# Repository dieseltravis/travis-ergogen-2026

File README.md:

# Travis's Ergogen v2026
This is a split keyboard with 2 ortholinear symmetrical 40-key halfs made with Ergogen v4. Multiple positions for an i2c OLED and mousewheel encoder. TRRS for connecting halfs, firmware not updated for that yet though.

## Parts:

JLCPCB SMD components (40 each per board):
* capacitor C710467
* diode C7420318
* RGB LED C5378731
* MX C41430893

Other parts:
* MCU: RP2040 Community Edition
* capacitor 6.3V 1000uF
* resistors 510k ohm (2 per board)
* 2u stabilizers (2 per board)
* TRRS PJ-320A jacks (2 per board if connecting)
* mousewheel encoder (like Alps-EC10E1220501)
* OLED i2c
* MX switches (40 per board)
* low-profile sockets/pins for MCU & OLED

## References:
My previous ergogen abominations:
* [travis-ergogen-numpad](https://github.com/dieseltravis/travis-ergogen-numpad)
* [travis-ergogen-2024](https://github.com/dieseltravis/travis-ergogen-2024)

### Footprints:
* https://github.com/ceoloide/ergogen-footprints
* https://github.com/dieseltravis/ergogen-footprints-travis

## Tips:

### Font used:
```
brew install --cask font-3270-nerd-font
```
https://www.nerdfonts.com/font-downloads

### Routing widths used:
```
"track_widths": [
        0.0,
        0.254,
        0.3556,
        0.508,
        1.27
      ],
```

### For STL arcs
It is buggy, set toJscadScript's maxArcFacet in Ergogen's cases.js, example locations on my machine:
```
./node_modules/ergogen/src/cases.js
~/.local/share/mise/installs/node/24.13.0/lib/node_modules/ergogen/src/cases.js
```
Note: the arcs are *super* glitchy in STLs

### For weird `node\r:` error:
```
find ./node_modules/ -type f -print0 | xargs -0 dos2unix --
```

## TODO:
* ~board: make those weird bottom shapes nicer~
* plate: print a 2u stab test key
    * ~print a top key test to measure for interference with i2c~
* ~i2c: if plate doesn't interfere with bottom ones remove top ones~
    * ~trrs: if top ones are removed, move left trrs to left side~
* case: just use flat one, arcs get too glitchy
* ~routing~
* ~bom: use [kicad-jlcpcb-tools plugin](https://github.com/Bouni/kicad-jlcpcb-tools)~
* ~leds: generate positions~
* ~qmk firmware~
    * ~via support~
* then arrowpad

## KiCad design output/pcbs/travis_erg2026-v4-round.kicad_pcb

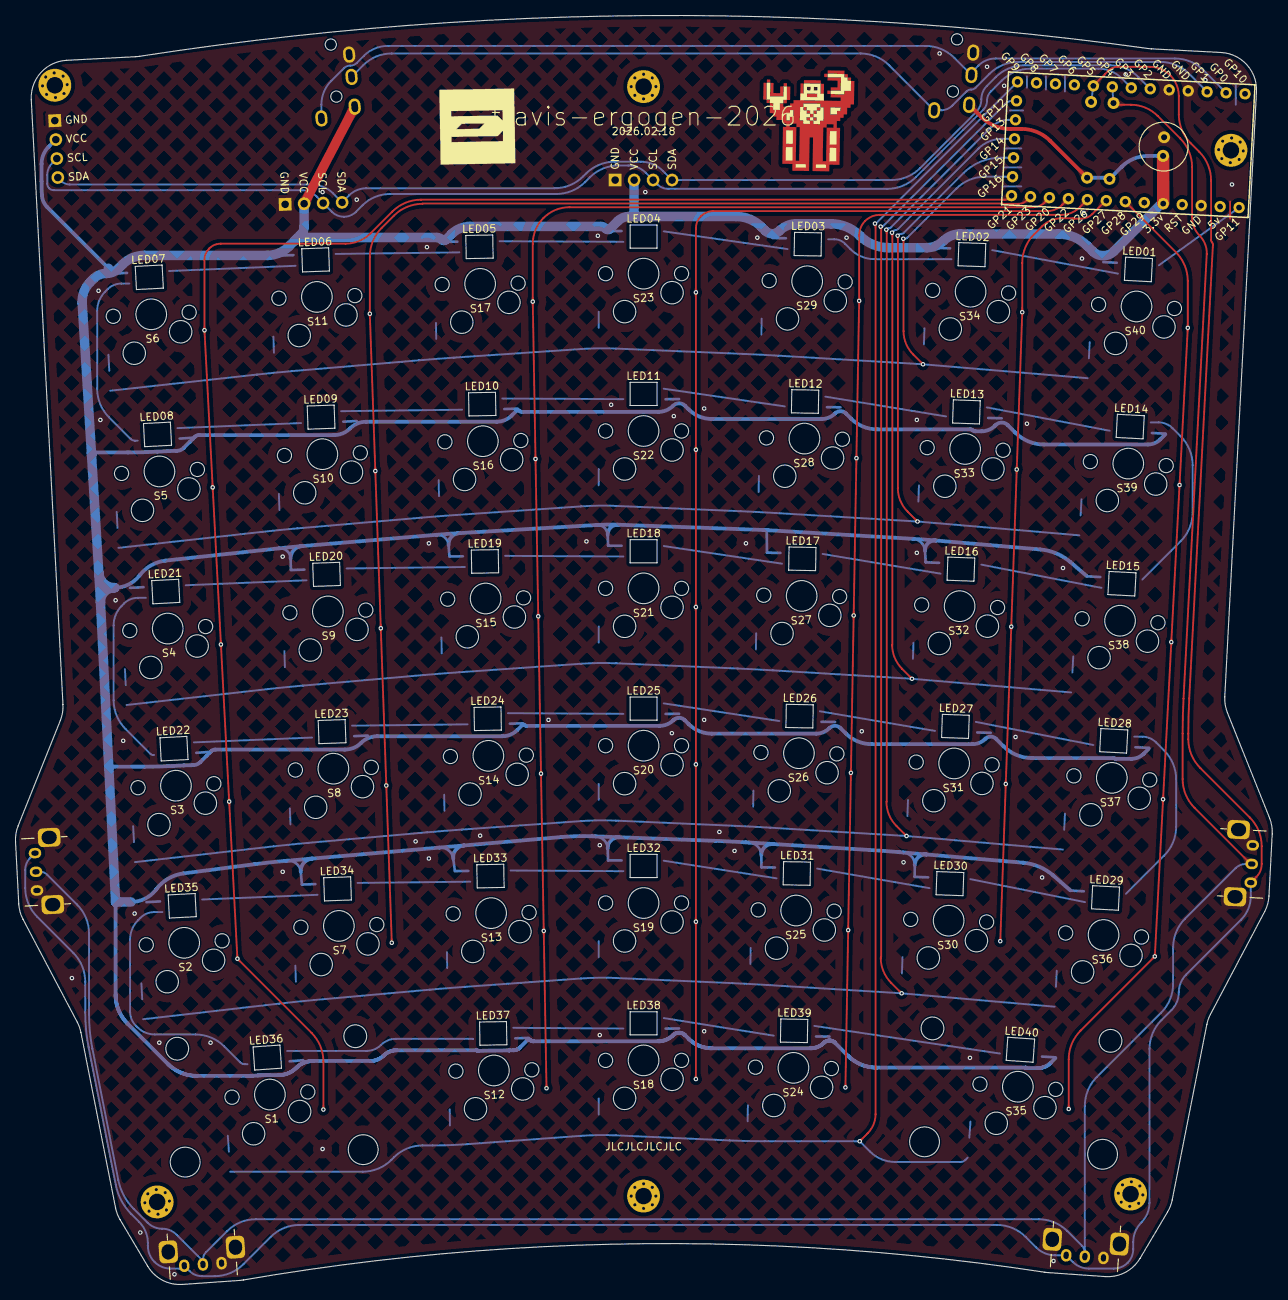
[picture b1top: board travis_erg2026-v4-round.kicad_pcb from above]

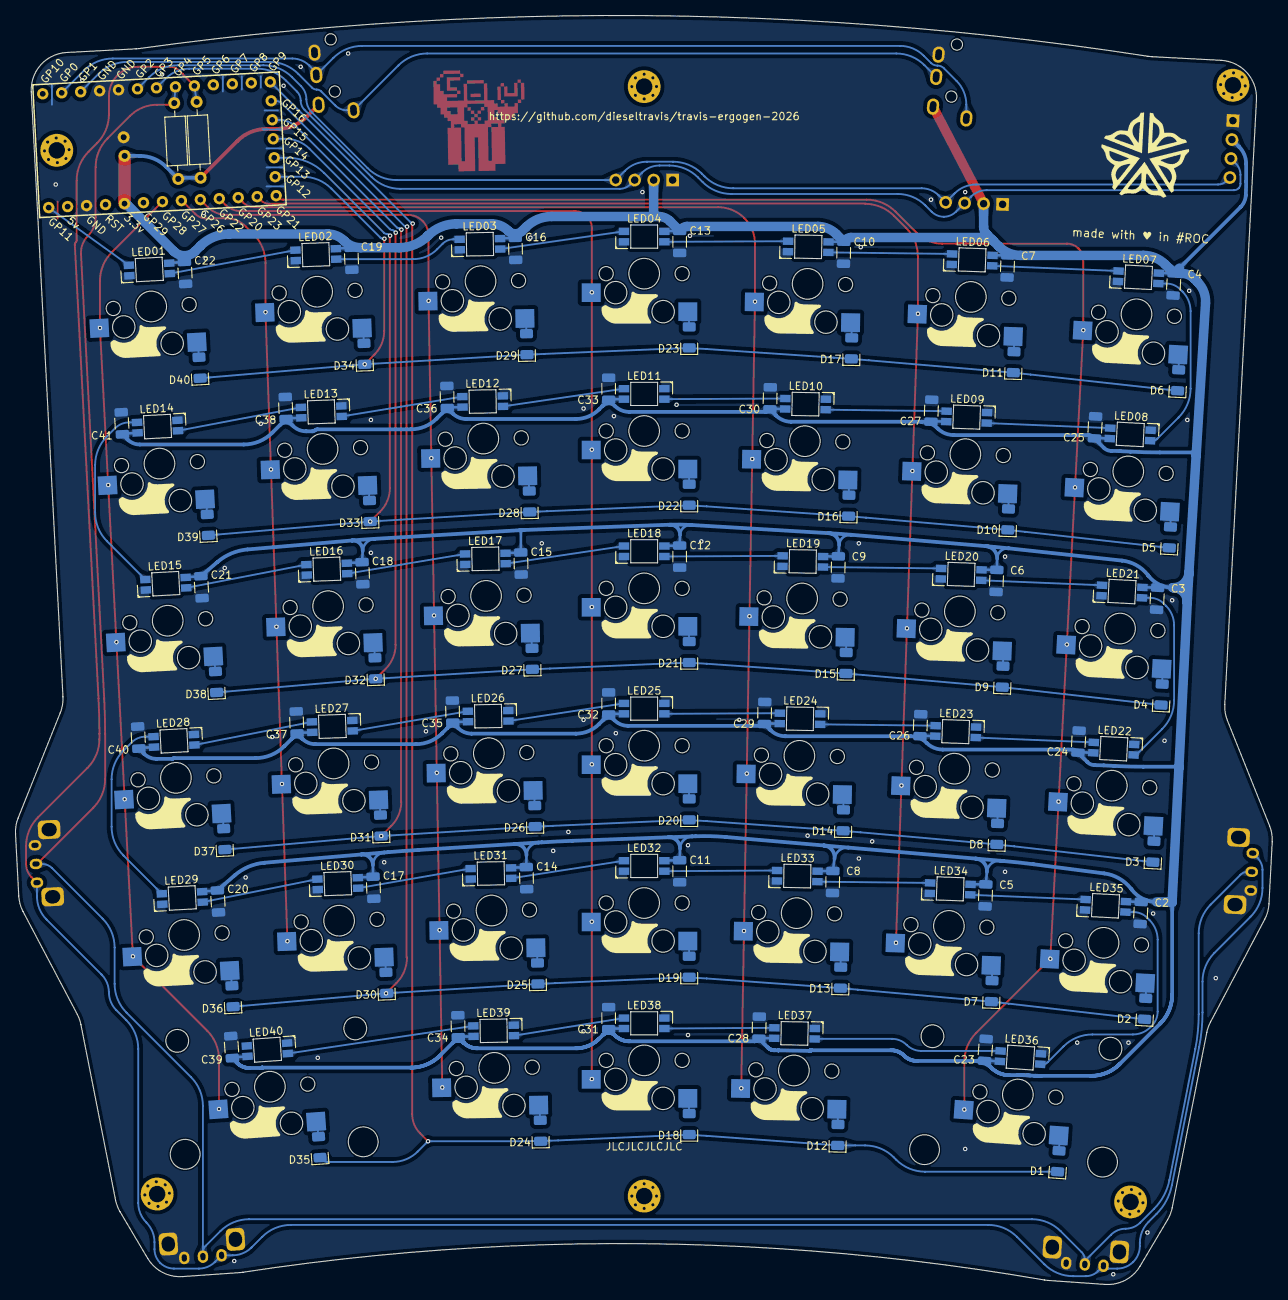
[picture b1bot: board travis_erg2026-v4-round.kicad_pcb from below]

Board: 2 copper layers, 168.1 x 169.8 mm, 184 parts (163 on the bottom side), 101 nets.

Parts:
C1: 6.3V 1000uF; C_Radial_D6.3mm_H11.0mm_P2.50mm
C2, C3, C4, C5, C6, C7, C8, C9, C10, C11, C12, C13, C14, C15, C16, C17, C18, C19, C20, C21, C22, C23, C24, C25, C26, C27, C28, C29, C30, C31, C32, C33, C34, C35, C36, C37, C38, C39, C40, C41: C710467; C_1206_3216Metric
D1, D2, D3, D4, D5, D6, D7, D8, D9, D10, D11, D12, D13, D14, D15, D16, D17, D18, D19, D20, D21, D22, D23, D24, D25, D26, D27, D28, D29, D30, D31, D32, D33, D34, D35, D36, D37, D38, D39, D40: C7420318; D_1206_3216Metric
HOLE1, HOLE2, HOLE3, HOLE4, HOLE5, HOLE6: MountingHole_2.2mm_M2_Pad_Via
LED01, LED02, LED03, LED04, LED05, LED06, LED07, LED08, LED09, LED10, LED11, LED12, LED13, LED14, LED15, LED16, LED17, LED18, LED19, LED20, LED21, LED22, LED23, LED24, LED25, LED26, LED27, LED28, LED29, LED30, LED31, LED32, LED33, LED34, LED35, LED36, LED37, LED38, LED39, LED40: C5378731; led_SK6812mini-e (per-key, single-side)
LOGO1: utility_ergogen_logo
LOGO2: travis
MCU1: RP2040 Community Edition; RP2040_Pro_Micro
OLED1, OLED2, OLED3: I2C_Breakout
R1, R2: 510k; R_Axial_DIN0207_L6.3mm_D2.5mm_P10.16mm_Horizontal
ROC1: travis
ROT1, ROT2, ROT3, ROT4: EC10E1220501; Alps-EC10E1220501
S1, S2, S3, S4, S5, S6, S7, S8, S9, S10, S11, S12, S13, S14, S15, S16, S17, S18, S19, S20, S21, S22, S23, S24, S25, S26, S27, S28, S29, S30, S31, S32, S33, S34, S35, S36, S37, S38, S39, S40: C41430893; switch_mx
STAB2u1, STAB2u2: Stabilizer_MX_2.00u
TRRS1, TRRS2: trrs_pj320a

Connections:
GND: C1.2, C2.2, C3.2, C4.2, C5.2, C6.2, C7.2, C8.2, C9.2, C10.2, C11.2, C12.2, C13.2, C14.2, C15.2, C16.2, C17.2, C18.2, C19.2, C20.2, C21.2, C22.2, C23.2, C24.2, C25.2, C26.2, C27.2, C28.2, C29.2, C30.2, C31.2, C32.2, C33.2, C34.2, C35.2, C36.2, C37.2, C38.2, C39.2, C40.2, C41.2, LED01.3, LED02.3, LED03.3, LED04.3, LED05.3, LED06.3, LED07.3, LED08.3, LED09.3, LED10.3, LED11.3, LED12.3, LED13.3, LED14.3, LED15.3, LED16.3, LED17.3, LED18.3, LED19.3, LED20.3, LED21.3, LED22.3, LED23.3, LED24.3, LED25.3, LED26.3, LED27.3, LED28.3, LED29.3, LED30.3, LED31.3, LED32.3, LED33.3, LED34.3, LED35.3, LED36.3, LED37.3, LED38.3, LED39.3, LED40.3, MCU1.4, MCU1.5, MCU1.29, OLED1.1, OLED2.1, OLED3.1, ROT1.4, ROT1.C, ROT2.4, ROT2.C, ROT3.4, ROT3.C, ROT4.4, ROT4.C, TRRS1.2, TRRS2.2
LED01: LED01.4, MCU1.31
LED02: LED01.2, LED02.4
LED03: LED02.2, LED03.4
LED04: LED03.2, LED04.4
LED05: LED04.2, LED05.4
LED06: LED05.2, LED06.4
LED07: LED06.2, LED07.4
LED08: LED07.2, LED08.4
LED09: LED08.2, LED09.4
LED10: LED09.2, LED10.4
LED11: LED10.2, LED11.4
LED12: LED11.2, LED12.4
LED13: LED12.2, LED13.4
LED14: LED13.2, LED14.4
LED15: LED14.2, LED15.4
LED16: LED15.2, LED16.4
LED17: LED16.2, LED17.4
LED18: LED17.2, LED18.4
LED19: LED18.2, LED19.4
LED20: LED19.2, LED20.4
LED21: LED20.2, LED21.4
LED22: LED21.2, LED22.4
LED23: LED22.2, LED23.4
LED24: LED23.2, LED24.4
LED25: LED24.2, LED25.4
LED26: LED25.2, LED26.4
LED27: LED26.2, LED27.4
LED28: LED27.2, LED28.4
LED29: LED28.2, LED29.4
LED30: LED29.2, LED30.4
LED31: LED30.2, LED31.4
LED32: LED31.2, LED32.4
LED33: LED32.2, LED33.4
LED34: LED33.2, LED34.4
LED35: LED34.2, LED35.4
LED36: LED35.2, LED36.4
LED37: LED36.2, LED37.4
LED38: LED37.2, LED38.4
LED39: LED38.2, LED39.4
LED40: LED39.2, LED40.4
RX: MCU1.3, TRRS1.3, TRRS2.5
TX: MCU1.2, TRRS1.5, TRRS2.3
VCC: C1.1, C2.1, C3.1, C4.1, C5.1, C6.1, C7.1, C8.1, C9.1, C10.1, C11.1, C12.1, C13.1, C14.1, C15.1, C16.1, C17.1, C18.1, C19.1, C20.1, C21.1, C22.1, C23.1, C24.1, C25.1, C26.1, C27.1, C28.1, C29.1, C30.1, C31.1, C32.1, C33.1, C34.1, C35.1, C36.1, C37.1, C38.1, C39.1, C40.1, C41.1, LED01.1, LED02.1, LED03.1, LED04.1, LED05.1, LED06.1, LED07.1, LED08.1, LED09.1, LED10.1, LED11.1, LED12.1, LED13.1, LED14.1, LED15.1, LED16.1, LED17.1, LED18.1, LED19.1, LED20.1, LED21.1, LED22.1, LED23.1, LED24.1, LED25.1, LED26.1, LED27.1, LED28.1, LED29.1, LED30.1, LED31.1, LED32.1, LED33.1, LED34.1, LED35.1, LED36.1, LED37.1, LED38.1, LED39.1, LED40.1, MCU1.27, OLED1.2, OLED2.2, OLED3.2, R1.1, R2.1, TRRS1.4, TRRS2.4
col0: MCU1.19, S1.1, S2.1, S3.1, S4.1, S5.1, S6.1
col1: MCU1.20, S7.1, S8.1, S9.1, S10.1, S11.1
col2: MCU1.21, S12.1, S13.1, S14.1, S15.1, S16.1, S17.1
col3: MCU1.22, S18.1, S19.1, S20.1, S21.1, S22.1, S23.1
col4: MCU1.23, S24.1, S25.1, S26.1, S27.1, S28.1, S29.1
col5: MCU1.24, S30.1, S31.1, S32.1, S33.1, S34.1
col6: MCU1.25, S35.1, S36.1, S37.1, S38.1, S39.1, S40.1
encA: MCU1.9, R1.2, ROT1.A, ROT2.A, ROT3.A, ROT4.A
encB: MCU1.8, R2.2, ROT1.B, ROT2.B, ROT3.B, ROT4.B
matrix_col0_row0: D1.2, S1.2
matrix_col0_row1: D2.2, S2.2
matrix_col0_row2: D3.2, S3.2
matrix_col0_row3: D4.2, S4.2
matrix_col0_row4: D5.2, S5.2
matrix_col0_row5: D6.2, S6.2
matrix_col1_row1: D7.2, S7.2
matrix_col1_row2: D8.2, S8.2
matrix_col1_row3: D9.2, S9.2
matrix_col1_row4: D10.2, S10.2
matrix_col1_row5: D11.2, S11.2
matrix_col2_row0: D12.2, S12.2
matrix_col2_row1: D13.2, S13.2
matrix_col2_row2: D14.2, S14.2
matrix_col2_row3: D15.2, S15.2
matrix_col2_row4: D16.2, S16.2
matrix_col2_row5: D17.2, S17.2
matrix_col3_row0: D18.2, S18.2
matrix_col3_row1: D19.2, S19.2
matrix_col3_row2: D20.2, S20.2
matrix_col3_row3: D21.2, S21.2
matrix_col3_row4: D22.2, S22.2
matrix_col3_row5: D23.2, S23.2
matrix_col4_row0: D24.2, S24.2
matrix_col4_row1: D25.2, S25.2
matrix_col4_row2: D26.2, S26.2
matrix_col4_row3: D27.2, S27.2
matrix_col4_row4: D28.2, S28.2
matrix_col4_row5: D29.2, S29.2
matrix_col5_row1: D30.2, S30.2
matrix_col5_row2: D31.2, S31.2
matrix_col5_row3: D32.2, S32.2
matrix_col5_row4: D33.2, S33.2
matrix_col5_row5: D34.2, S34.2
matrix_col6_row0: D35.2, S35.2
matrix_col6_row1: D36.2, S36.2
matrix_col6_row2: D37.2, S37.2
matrix_col6_row3: D38.2, S38.2
matrix_col6_row4: D39.2, S39.2
matrix_col6_row5: D40.2, S40.2
row0: D1.1, D12.1, D18.1, D24.1, D35.1, MCU1.13
row1: D2.1, D7.1, D13.1, D19.1, D25.1, D30.1, D36.1, MCU1.14
row2: D3.1, D8.1, D14.1, D20.1, D26.1, D31.1, D37.1, MCU1.15
row3: D4.1, D9.1, D15.1, D21.1, D27.1, D32.1, D38.1, MCU1.16
row4: D5.1, D10.1, D16.1, D22.1, D28.1, D33.1, D39.1, MCU1.17
row5: D6.1, D11.1, D17.1, D23.1, D29.1, D34.1, D40.1, MCU1.18
scl: MCU1.7, OLED1.3, OLED2.3, OLED3.3
sda: MCU1.6, OLED1.4, OLED2.4, OLED3.4

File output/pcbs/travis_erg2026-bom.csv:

"Id";"Designator";"Footprint";"Quantity";"Designation";"Supplier and ref";
1;"MCU1";"RP2040_Pro_Micro";1;"RP2040 Pro Micro";;;
2;"C1";"C_Radial_D6.3mm_H11.0mm_P2.50mm";1;"6.3V 1000uF";;;
3;"OLED1,OLED2,OLED3,OLED4,OLED5";"I2C_Breakout";5;"I2C_Breakout";;;
4;"ROT1,ROT2,ROT3,ROT4";"Alps-EC10E1220501";4;"EC10E1220501";;;
5;"S1,S2,S3,S4,S5,S6,S7,S8,S9,S10,S11,S12,S13,S14,S15,S16,S17,S18,S19,S20,S21,S22,S23,S24,S25,S26,S27,S28,S29,S30,S31,S32,S33,S34,S35,S36,S37,S38,S39,S40";"MX";40;"C41430893";;;
6;"D1,D2,D3,D4,D5,D6,D7,D8,D9,D10,D11,D12,D13,D14,D15,D16,D17,D18,D19,D20,D21,D22,D23,D24,D25,D26,D27,D28,D29,D30,D31,D32,D33,D34,D35,D36,D37,D38,D39,D40";"D_1206_3216Metric";40;"D_1206_3216Metric";;;
7;"LED1,LED2,LED3,LED4,LED5,LED6,LED7,LED8,LED9,LED10,LED11,LED12,LED13,LED14,LED15,LED16,LED17,LED18,LED19,LED20,LED21,LED22,LED23,LED24,LED25,LED26,LED27,LED28,LED29,LED30,LED31,LED32,LED33,LED34,LED35,LED36,LED37,LED38,LED39,LED40";"led_SK6812mini-e (per-key, single-side)";40;"C5378731";;;
8;"C2,C3,C4,C5,C6,C7,C8,C9,C10,C11,C12,C13,C14,C15,C16,C17,C18,C19,C20,C21,C22,C23,C24,C25,C26,C27,C28,C29,C30,C31,C32,C33,C34,C35,C36,C37,C38,C39,C40,C41";"C_1206_3216Metric";40;"C710467";;;
9;"HOLE1,HOLE2,HOLE3,HOLE4,HOLE5,HOLE6";"MountingHole_2.2mm_M2_Pad_Via";6;"";;;

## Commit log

2025-11-08 initial
2025-11-08 update submodule
2025-11-08 builb
2025-11-08 leds
2025-11-09 pcb generation
2026-01-18 led caps
2026-01-18 stabs, diodes, caps labels
2026-01-19 holes, oled options
2026-01-19 scotto keebs 2040 promicro
2026-01-19 adjusted to fit
2026-01-20 todos
2026-01-21 removing to add the right way
2026-01-21 rm -rf
2026-01-21 Update footprint submodule
2026-01-21 Remove footprint submodule
2026-01-21 update modules
2026-01-21 travis footprints submodule
2026-01-21 testing footprints
2026-01-23 update board with room and i2c headers
2026-01-24 board updates, hole updates
2026-01-24 footprint updates, wheels, holes
2026-01-24 minor updates
2026-01-24 update mounting
2026-01-24 case standoff adjustments
2026-01-25 refinements for kicad
2026-01-26 bunch of documentation
2026-01-27 BOM and CPL progress
2026-01-28 testing zmk
2026-01-30 attempt 2
2026-01-30 footprints?
2026-01-31 v2 wired
2026-01-31 rounded version
2026-02-01 fix encorder, organize datasheets, add easy routes and vias
2026-02-03 v3 routed
2026-02-03 jlc pcb bom and pos
2026-02-06 plate
2026-02-08 trrs, corners
2026-02-08 footprint updates
2026-02-10 trrs data sheet
2026-02-13 arcs are messed up
2026-02-13 yarn upgrade and arcs in progress
2026-02-14 progress
2026-02-14 models
2026-02-15 plate refinements
2026-02-15 updated TODOs
2026-02-16 board outline update, qmk start
2026-02-16 qmk/led progress
2026-02-17 qmk progress
2026-02-18 successful compilation
2026-02-19 pin fix
2026-02-19 symmetry fixes
2026-02-22 v4, rounded
2026-02-22 readme
